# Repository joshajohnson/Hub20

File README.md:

# Hub20

Hub20 is a numpad with a bunch of features you never knew you needed. They include:

- Left and Right handed layouts supported, along with a 4x5 1U grid enabling it to be used as a macropad.
- Two rotary encoders, enabling intuitive controls for a wide range of tools including CAD and photo / video editing.
- Inbuilt USB 2.0 Hub with Type-C connectors, allowing connection to other keyboards, memory sticks, wireless receivers and more!
- VIA and QMK compatibility, including a "macro" mode enabling the keys to be remapped on a host computer.
- 27 addressable RGB leds, including one under each key.

If this project looks familiar, it's because it contains all the best parts of [Hub16](https://github.com/joshajohnson/Hub16), with a few added extras.

## Project Status

Hardware is finalised and kits can be purchased from [Tindie](https://www.tindie.com/products/joshajohnson/hub20-programmable-macro-numberpad/).

## Getting Started Guide

- [Keyboard Assembly](documents/keyboard-assembly.md)
- [VIA Keymap Configuration](documents/via.md)
- [Macro Configuration](documents/macro.md)

## Detailed Info

- [Advanced Firmware / Software Configuration](documents/advanced-config.md)
- [PCB SMT Assembly Guide](documents/pcba.md)
- [Enclosure Manufacturing](documents/enclosure.md)

### Repo Contents

- `documents` contains all documentation and images for the project.
- `firmware` contains both the source and precompiled binaries for Hub20.
- `hardware` contains the KiCad design files for the keyboard.
- `josh-kicad-lib` is my personal KiCad parts library which contains many of the parts used.
- `scripts` contains a number of scripts used in the PCB design process.
- `mechanicals` contain the plate and case design for Hub20.
- `production` contains all the files required to produce the PCB. It also contains test scripts and jigs.
- `software` contains all the VIA config, along with template script to use Hub20 as a macropad with software on your computer.

### Notes on the USB Hub

The hub is a four port USB 2.0 Hub with Type-C connectors, aimed at allowing connection of keyboards, mice, memory sticks, wireless receivers, and other small devices (including a second Hub20!)  to your computer.

Due to cost and space constraints, the hub has some limitations. The hub **is not**:

- USB 3.x, Power Delivery, Thunderbolt, DisplayPort, etc compatible. 
- Designed to charge your phone quickly. Only 100mA is guaranteed per port.
- Designed to work with power hungry devices such as spinning hard drives.
- Guaranteed to provide full USB 2.0 speeds and performance on all ports.

Might you be able to charge your phone whilst copying files at full speed of a spinning hard drive over a long cable? Maybe. However Hub20 is a numpad first, USB hub second, so if you are looking for a high performance device I'd suggest picking up a dedicated USB hub and just using Hub20 as a numpad.

If you have any questions or comments please get in touch. I can be found on Discord as `_joshajohnson#9451`, [Twitter](https://twitter.com/_joshajohnson), email, or leave an issue or pull request on this repo.

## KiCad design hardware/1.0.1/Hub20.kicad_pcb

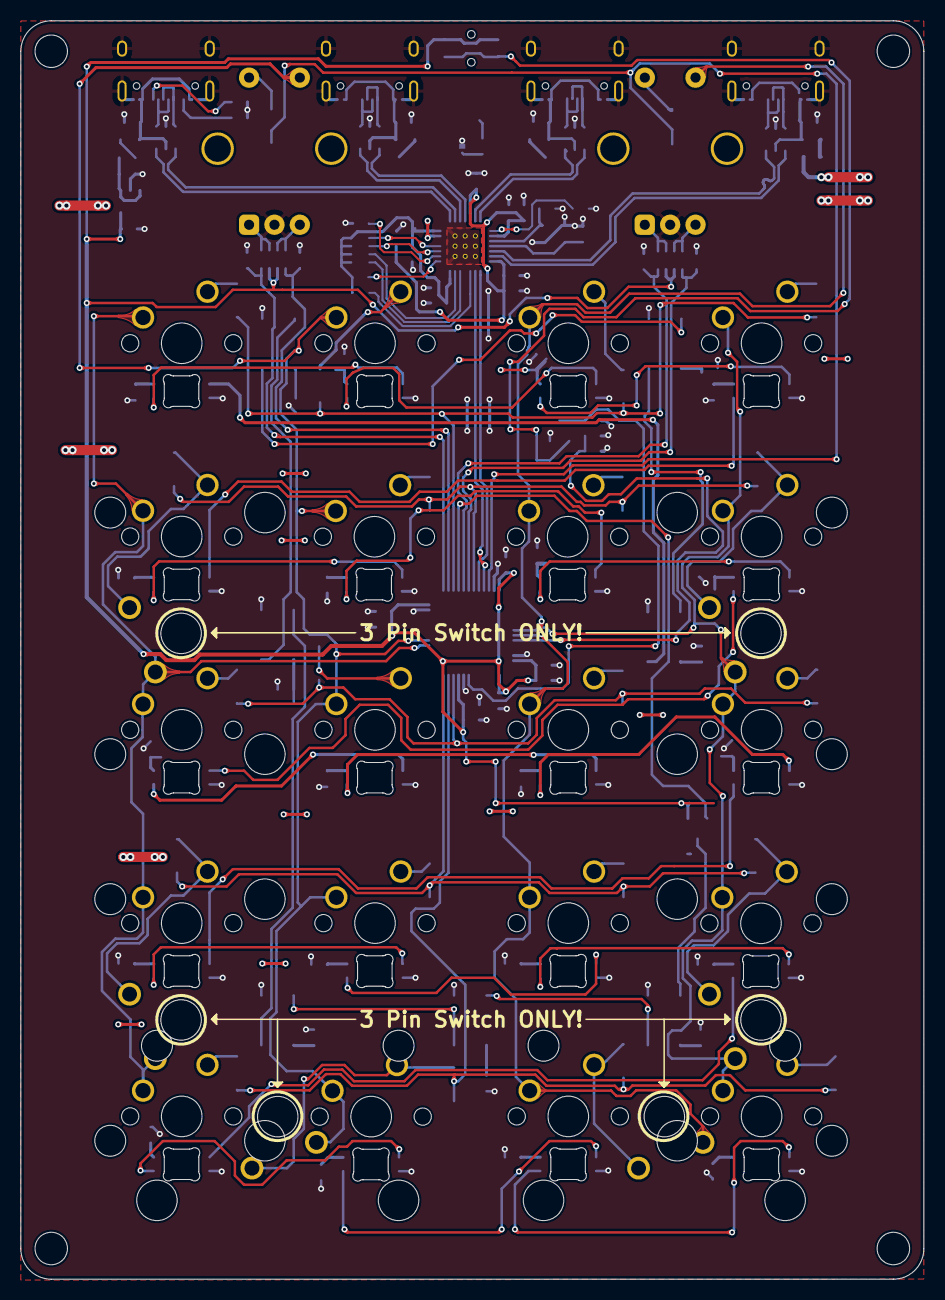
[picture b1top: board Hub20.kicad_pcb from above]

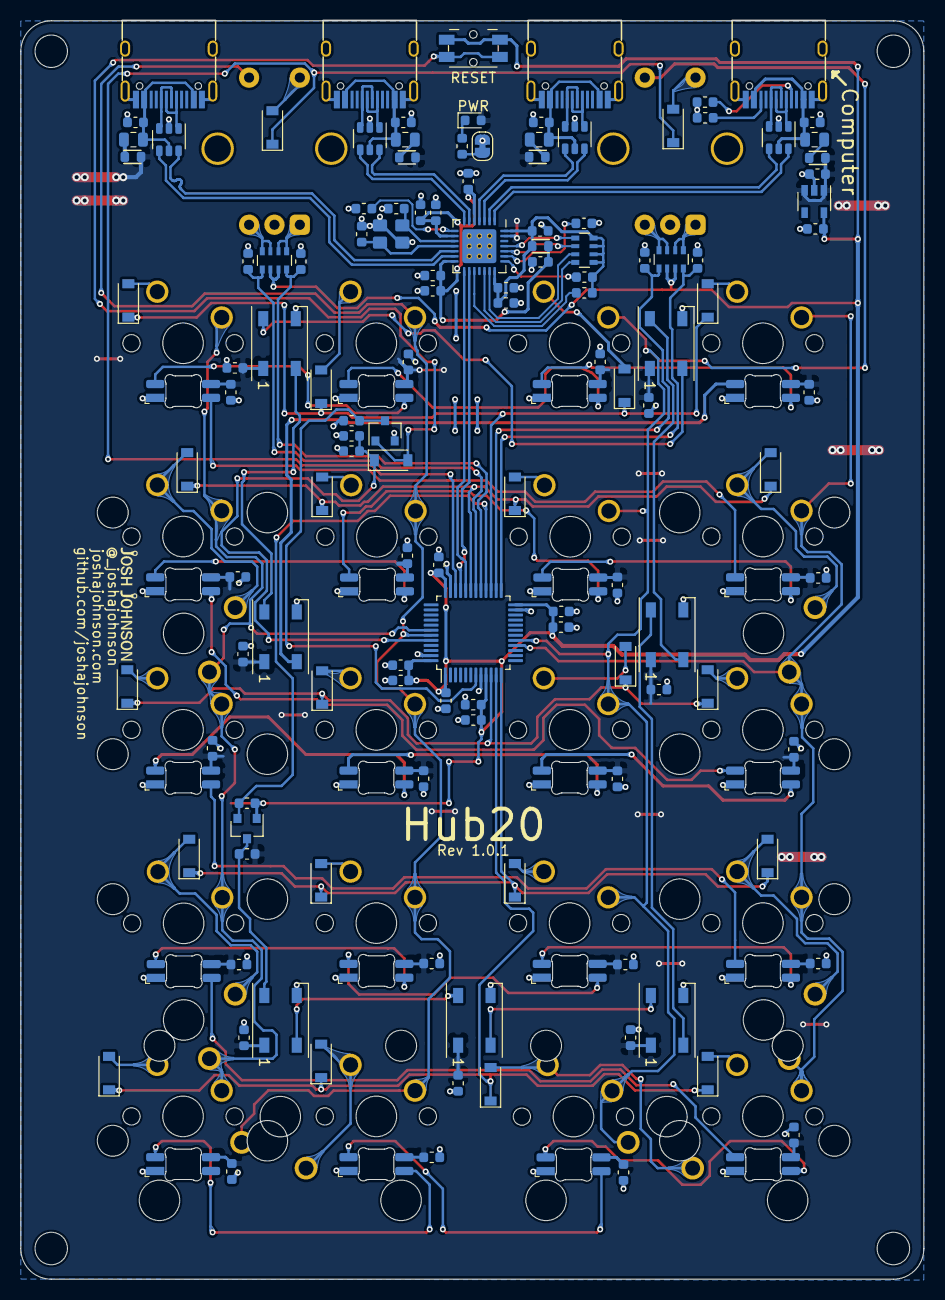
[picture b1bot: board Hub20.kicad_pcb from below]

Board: 2 copper layers, 89.0 x 124.0 mm, 183 parts (151 on the bottom side), 116 nets.

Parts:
C1, C4, C5, C6, C7, C8, C9, C11, C12, C13, C15, C16, C17, C21, C22, C23, C24, C25, C26, C27, C29, C30, C31, C33, C35, C36, C37, C38, C39, C40, C42, C43, C46, C47, C48, C49, C50, C51, C52, C53, C56, C58, C59, C60: 100n; C_0603_1608Metric
C10, C19, C28, C32, C34, C54, C55, C57: 1u; C_0603_1608Metric
C14, C20, C41: 10u; C_0603_1608Metric
C18: 4u7; C_0603_1608Metric
C44, C45: 15p; C_0603_1608Metric
D1, D4, D5, D6, D7, D8, D10, D11, D12, D13, D14, D16, D18, D19, D20, D21, D22, D24, D25, D26, D27, D28, D29: 1N4148; D_SOD-123
D2, D3, D9, D15, D17, D23, D30: WS2812B; LED_WS2812B_PLCC4_5.0x5.0mm_P3.2mm
D31, D33, D34, D35, D36, D37, D38, D39, D40, D41, D42, D43, D44, D45, D46, D47, D48, D49, D50, D51: SK6812MINI-E; DUMMY_SK6812MINI-E
D32: LED; LED_0603_1608Metric
F1: 1A; Fuse_0805_2012Metric
F2, F3, F4: 500mA; Fuse_0805_2012Metric
FB1, FB2, FB3, FB4, FB5: 600R; Ferrite_Bead_0603
H1, H2, H3, H4: M3; MountingHole_3.2mm_M3
J1, J2, J3, J4: USB_C_Receptacle_USB2.0; USB_C_U262-161N-4BVC11
JP1: LED; SolderJumper-2_P1.3mm_Bridged_RoundedPad1.0x1.5mm
LOGO1: Josh-Details; josh-details
LOGO2: Board-Title; board-title
LOGO3: Josh-Logo; josh-johnson-logo-11x2
LOGO5: OSHW; OSHW-Logo2_9.8x8mm_Mask
MX1, MX2: 2U; MXOnly-2U-NoLED-3PIN
MX3, MX4, MX5, MX6: 2U; MXOnly-2U-ReversedStabilizers-NoLED-3PIN
Q1: DTC123J; SOT-23
Q2: BSS138; SOT-23
R2, R3, R14: 5K1; R_0603_1608Metric
R4: 100K; R_0603_1608Metric
R5, R6, R7, R8, R9: 10K; R_0603_1608Metric
R10: 649R; R_0603_1608Metric
RN1, RN2, RN3: 10K; R_Array_Convex_4x0603
SW1: EVQPUL; Panasonic_EVQPUL_EVQPUC
SW2, SW3, SW4, SW5, SW6, SW8, SW9, SW10, SW11, SW12, SW14, SW15, SW16, SW17, SW18, SW19, SW20, SW21, SW22, SW23: MX_RGB; MX_KEYSWITCH_RGB
SW7, SW13: EC11; RotaryEncoder_Alps_EC11E-Switch_Vertical_H20mm_CircularMoun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
U1: AP2112K-3.3; SOT-23-5
U2, U6, U7, U8: USBLC6-2SC6; SOT-23-6
U3: STM32F072C8Tx; LQFP-48_7x7mm_P0.5mm
U5: CY7C65632-28LTXCT; QFN-28-1EP_5x5mm_P0.5mm_EP3.35x3.35mm_ThermalVias
Y1: 12MHz; Crystal_SMD_3225-4Pin_3.2x2.5mm

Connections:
+3.3VA: C42.1, C43.1, C46.1, C47.1, C54.1, C55.1, FB2.1, U5.5, U5.9, U5.14
+3.3VP: C41.1, C56.1, C57.1, FB2.2, R8.2, R9.2, RN3.5, RN3.6, RN3.7, RN3.8, U5.21, U5.28
+3V3: C19.1, C28.1, C32.1, C34.1, C36.1, C38.1, C40.1, C48.1, C49.1, Q2.1, R5.1, RN1.2, RN1.3, RN2.2, RN2.3, SW1.1, U1.5, U3.1, U3.9, U3.24, U3.36, U3.48
+5V: C1.1, C4.1, C5.1, C6.1, C7.1, C8.1, C9.1, C10.1, C11.1, C12.1, C13.1, C15.1, C16.1, C17.1, C21.1, C22.1, C23.1, C24.1, C25.1, C26.1, C27.1, C29.1, C30.1, C31.1, C33.1, C35.1, C37.1, C39.1, D2.1, D3.1, D9.1, D15.1, D17.1, D23.1, D30.1, D32.2, FB1.1, FB3.2, FB4.2, FB5.2, R6.1, SW2.5, SW3.5, SW4.5, SW5.5, SW6.5, SW8.5, SW9.5, SW10.5, SW11.5, SW12.5, SW14.5, SW15.5, SW16.5, SW17.5, SW18.5, SW19.5, SW20.5, SW21.5, SW22.5, SW23.5, U1.1, U1.3, U5.27
/BKLT: D30.2, SW2.3
/BOOT0: C20.1, D1.1, R4.1, U3.44
/C0: MX1.1, MX2.1, SW2.2, SW3.2, SW4.2, SW5.2, SW6.2, U3.16
/C1: MX3.1, SW7.S1, SW8.2, SW9.2, SW10.2, SW11.2, SW12.2, U3.17
/C2: MX4.1, SW13.S1, SW14.2, SW15.2, SW16.2, SW17.2, SW18.2, U3.43
/C3: MX5.1, MX6.1, SW19.2, SW20.2, SW21.2, SW22.2, SW23.2, U3.42
/E1A: RN1.5, RN1.6, SW7.A
/E1B: RN1.7, RN1.8, SW7.B
/E2A: RN2.5, RN2.6, SW13.A
/E2B: RN2.7, RN2.8, SW13.B
/ENC1A_DB: C50.1, RN1.4, U3.25
/ENC1B_DB: C52.1, RN1.1, U3.26
/ENC2A_DB: C51.1, RN2.4, U3.29
/ENC2B_DB: C53.1, RN2.1, U3.30
/LED: Q2.2, R5.2, U3.28
/LED_5V: D2.4, Q2.3, R6.2
/L_R1: SW3.3, SW19.4
/L_R2: SW4.3, SW20.4
/L_R3: SW5.3, SW21.4
/L_R4: SW6.3, SW22.4
/R0: D16.1, D24.1, U3.34
/R1: D4.1, D10.1, D18.1, D25.1, U3.27
/R2: D5.1, D11.1, D19.1, D26.1, U3.31
/R3: D6.1, D12.1, D20.1, D27.1, U3.10
/R4: D7.1, D13.1, D21.1, D28.1, U3.12
/R5: D8.1, D14.1, D22.1, D29.1, U3.11
/USB Hub/D1_D+: U5.4, U6.4
/USB Hub/D1_D-: U5.3, U6.6
/USB Hub/D2_D+: U5.7, U7.4
/USB Hub/D2_D-: U5.6, U7.6
/USB Hub/D3_D+: U5.13, U8.4
/USB Hub/D3_D-: U5.12, U8.6
/USB Hub/XIN: C44.1, U5.10, Y1.1
/USB Hub/XOUT: C45.1, U5.11, Y1.3
/USB Hub/nOVR_1: RN3.1, U5.25
/USB Hub/nOVR_2: RN3.2, U5.24
/USB Hub/nOVR_3: RN3.3, U5.20
/USB Hub/nOVR_4: RN3.4, U5.19
/USB+: J1.A6, J1.B6, U2.3
/USB-: J1.A7, J1.B7, U2.1
/USB_D+: U2.4, U5.2
/USB_D-: U2.6, U5.1
/USB_MCU_D+: U3.33, U5.16
/USB_MCU_D-: U3.32, U5.15
/nRST: C18.1, Q1.3, U3.7
GND: C1.2, C4.2, C5.2, C6.2, C7.2, C8.2, C9.2, C10.2, C11.2, C12.2, C13.2, C14.2, C15.2, C16.2, C17.2, C18.2, C19.2, C20.2, C21.2, C22.2, C23.2, C24.2, C25.2, C26.2, C27.2, C28.2, C29.2, C30.2, C31.2, C32.2, C33.2, C34.2, C35.2, C36.2, C37.2, C38.2, C39.2, C40.2, C41.2, C42.2, C43.2, C44.2, C45.2, C46.2, C47.2, C48.2, C49.2, C50.2, C51.2, C52.2, C53.2, C54.2, C55.2, C56.2, C57.2, C58.2, C59.2, C60.2, D2.3, D3.3, D9.3, D15.3, D17.3, D23.3, D30.3, J1.A1, J1.A12, J1.B1, J1.B12, J1.S1, J2.A1, J2.A12, J2.B1, J2.B12, J2.S1, J3.A1, J3.A12, J3.B1, J3.B12, J3.S1, J4.A1, J4.A12, J4.B1, J4.B12, J4.S1, JP1.2, Q1.2, R2.1, R3.1, R4.2, R7.2, R10.2, SW2.6, SW3.6, SW4.6, SW5.6, SW6.6, SW7.C, SW8.6, SW9.6, SW10.6, SW11.6, SW12.6, SW13.C, SW14.6, SW15.6, SW16.6, SW17.6, SW18.6, SW19.6, SW20.6, SW21.6, SW22.6, SW23.6, U1.2, U2.2, U3.8, U3.23, U3.35, U3.47, U5.29, U6.2, U7.2, U8.2, Y1.2, Y1.4
unnamed: C58.1, F2.1, J2.A4, J2.A9, J2.B4, J2.B9, U6.5
unnamed: C59.1, F3.1, J3.A4, J3.A9, J3.B4, J3.B9, U7.5
unnamed: C60.1, F4.1, J4.A4, J4.A9, J4.B4, J4.B9, U8.5
unnamed: D1.2, Q1.1, SW1.2
unnamed: D2.2, D3.4
unnamed: D3.2, D9.4
unnamed: D4.2, SW2.1
unnamed: D5.2, MX1.2, SW3.1
unnamed: D6.2, SW4.1
unnamed: D7.2, MX2.2, SW5.1
unnamed: D8.2, SW6.1
unnamed: D10.2, SW8.1
unnamed: D11.2, SW9.1
unnamed: D12.2, SW10.1
unnamed: D13.2, SW11.1
unnamed: D14.2, MX3.2, SW12.1
unnamed: D15.2, D17.4
unnamed: D9.2, D15.4
unnamed: D16.2, SW7.S2
unnamed: D17.2, D23.4
unnamed: D18.2, SW14.1
unnamed: D19.2, SW15.1
unnamed: D20.2, SW16.1
unnamed: D21.2, SW17.1
unnamed: D22.2, MX4.2, SW18.1
unnamed: D23.2, D30.4
unnamed: D24.2, SW13.S2
unnamed: D25.2, SW19.1
unnamed: D26.2, MX5.2, SW20.1
unnamed: D27.2, SW21.1
unnamed: D28.2, MX6.2, SW22.1
unnamed: D29.2, SW23.1
unnamed: D32.1, R14.1
unnamed: F1.1, FB1.2
unnamed: F2.2, FB3.1
unnamed: F3.2, FB4.1
unnamed: F4.2, FB5.1
unnamed: J1.A5, R2.2
unnamed: J1.B5, R3.2
unnamed: J2.A6, J2.B6, U6.3
unnamed: J2.A7, J2.B7, U6.1
unnamed: J3.A6, J3.B6, U7.3
unnamed: J3.A7, J3.B7, U7.1
unnamed: J4.A6, J4.B6, U8.3
unnamed: J4.A7, J4.B7, U8.1
unnamed: JP1.1, R14.2
unnamed: R7.1, U5.23
unnamed: R8.1, U5.17
unnamed: R9.1, U5.22
unnamed: R10.1, U5.8
unnamed: SW2.4, SW8.3
unnamed: SW3.4, SW9.3
unnamed: SW4.4, SW10.3
unnamed: SW10.4, SW16.3
unnamed: SW5.4, SW11.3
unnamed: SW11.4, SW17.3
unnamed: SW6.4, SW12.3
unnamed: SW12.4, SW18.3
unnamed: SW8.4, SW14.3
unnamed: SW14.4, SW19.3
unnamed: SW9.4, SW15.3
unnamed: SW15.4, SW20.3
unnamed: SW16.4, SW21.3
unnamed: SW17.4, SW22.3
unnamed: SW18.4, SW23.3
VBUS: C14.1, F1.2, J1.A4, J1.A9, J1.B4, J1.B9, U2.5

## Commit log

2020-07-04 add gitignore
2020-07-04 drc=erc=0
2020-07-04 clean up routing, design review TODO
2020-07-26 designs off to fab
2020-07-26 fit label locations
2020-07-26 add render + update readme
2020-08-08 start 0.2 layout
2020-08-09 layout getting close
2020-08-09 center encoders :/
2020-08-12 tidy up things
2020-08-12 improved ground return under USB hub
2020-08-12 now passing DRC
2020-08-16 side mounted rst + slik cleanup
2020-08-18 update plate
2020-08-19 stop touching the design josh
2020-08-19 move plates to mechanicals folder
2020-08-22 update BOM
2020-09-06 limit 2U to 3 pin only
2020-09-09 update fuse values
2020-09-14 1.0 production files ready
2020-09-20 add mechanicals
2020-10-06 begin documentation
2020-10-06 update via
2020-10-07 progress on documentation
2020-10-08 update advanced config and remove test instructions
2020-10-08 good enough for now
2020-10-08 remove unwanted file
2020-10-09 add firmware
2020-10-09 clean up files
2020-10-09 add ahk examples
2020-10-09 proof read
2020-10-09 --amend
2020-10-10 update test script + enclosure files
2020-11-28 add assembly instructions
2020-11-28 update link to assembly instructions
2020-11-28 update firmware
2020-11-29 add images to readme
2020-11-29 commonise spelling of bare-bones
2020-11-30 update link to tindie now avail
2020-11-30 link to VIA json instructions in build guide
2020-12-02 typo + fix switch usage
2020-12-10 update via download instructions
2021-01-16 update VIA instructions now it's merged
2021-02-11 firmware now merged upstream
2021-03-21 1.0.1 initial release
2021-03-21 add comment on removing protective paper
2021-06-20 update test files
2021-06-20 update pcb for production
2021-06-20 update assembly instructions
2021-06-26 clean up production files
